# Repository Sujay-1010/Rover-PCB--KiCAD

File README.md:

# Rover-PCB--KiCAD
Following pcb contains a rover pcb design, its schematics, its bom(bill of materials), and the working paramters of all the components used.

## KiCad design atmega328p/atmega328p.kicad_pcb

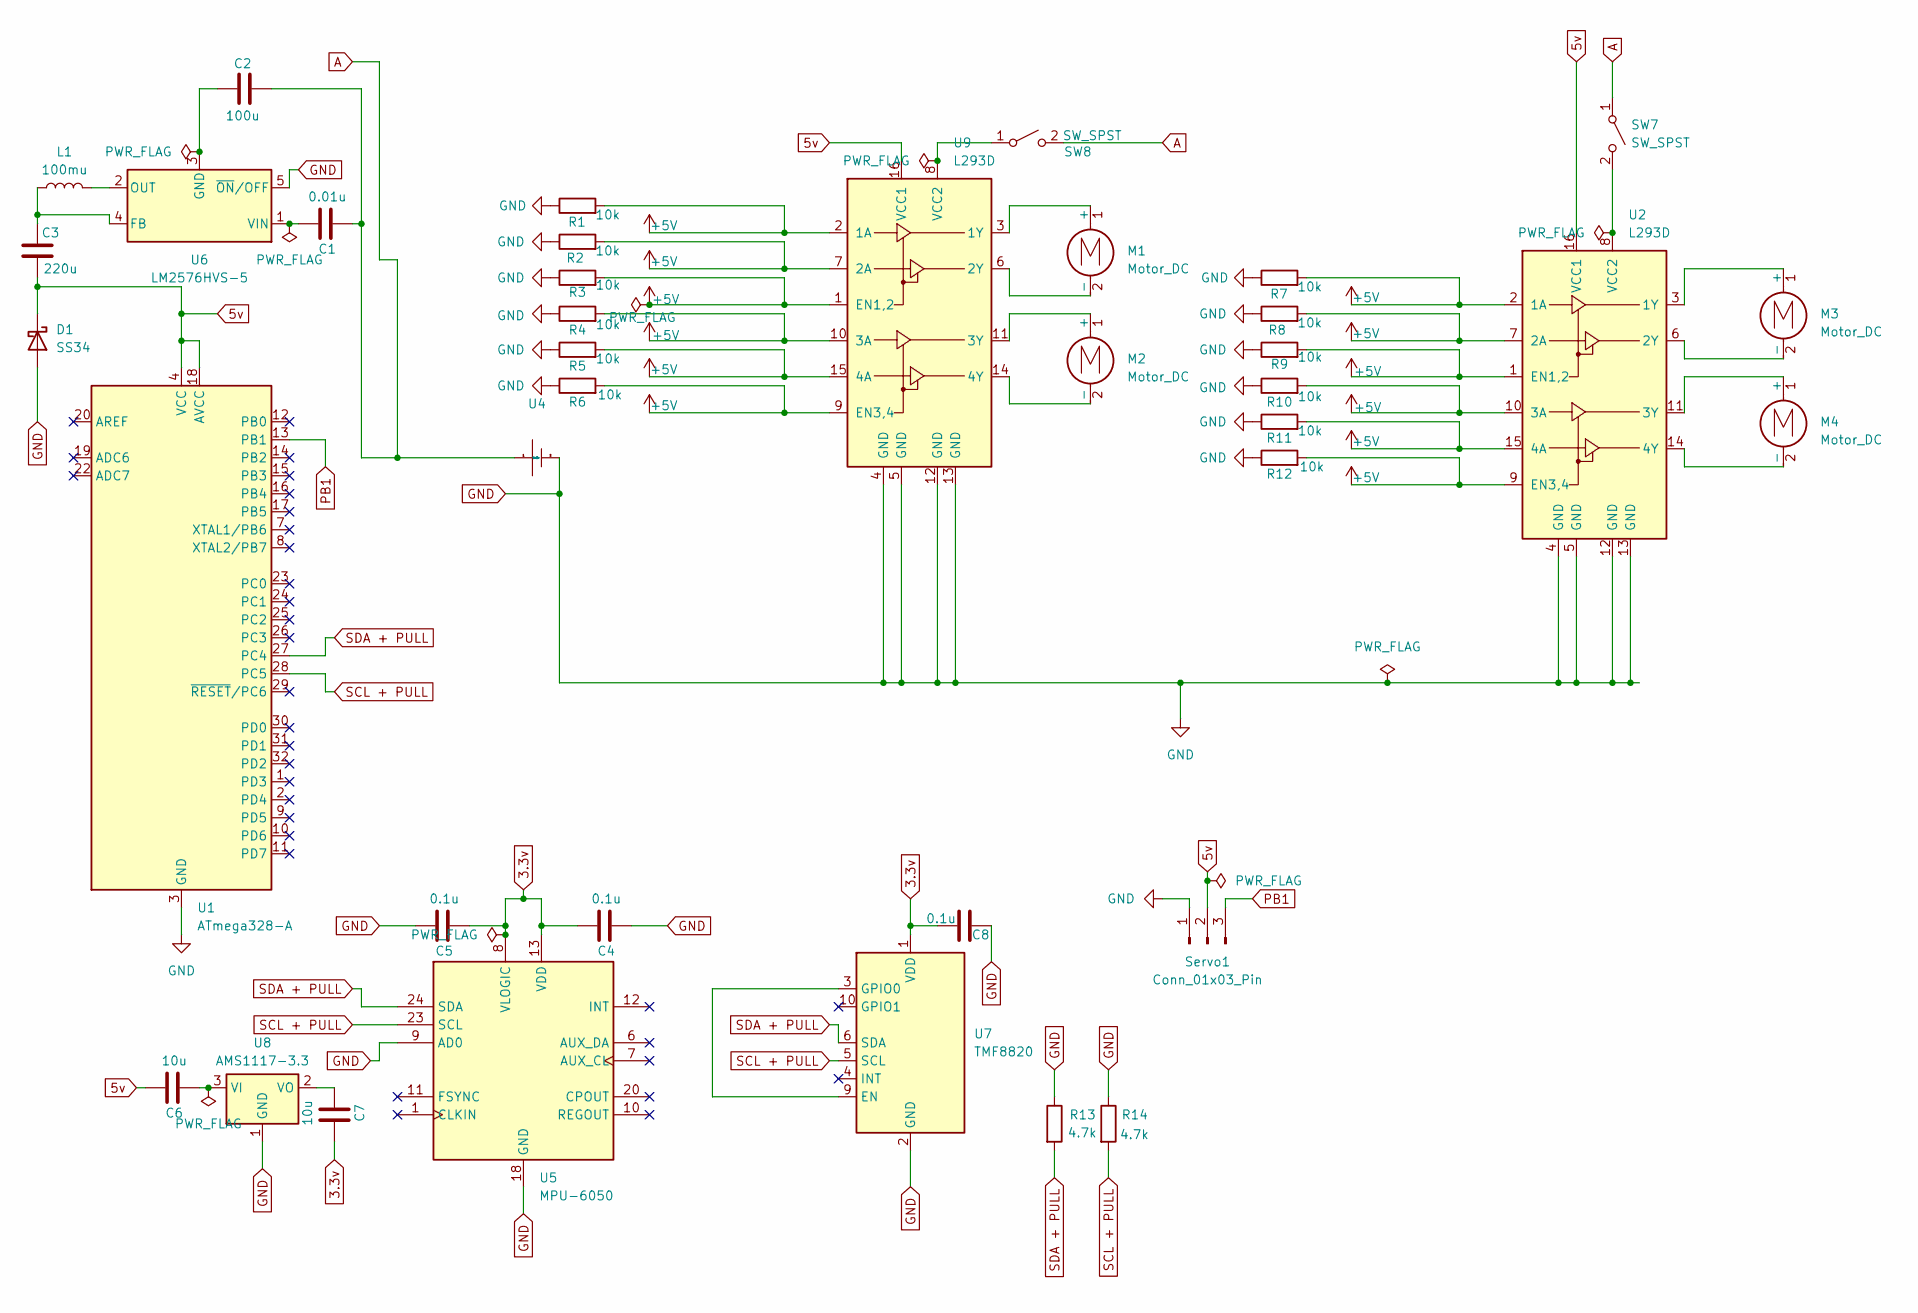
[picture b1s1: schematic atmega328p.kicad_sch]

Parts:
C1: 0.01u; C_0603_1608Metric
C2: 100u; C_0603_1608Metric
C3: 220u; C_0603_1608Metric
C4, C5, C8: 0.1u; C_0603_1608Metric
C6, C7: 10u; C_0805_2012Metric
D1: SS34; D_SMA
L1: 100mu; L_10.4x10.4_H4.8
M1, M2, M3, M4: Motor_DC; TerminalBlock_Phoenix_MKDS-1,5-2-5.08_1x02_P5.08mm_Horizont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
R1, R2, R3, R4, R5, R6, R7, R8, R9, R10, R11, R12: 10k; R_0603_1608Metric
R13, R14: 4.7k; R_0603_1608Metric
SW7, SW8: SW_SPST; SW_Push_1P1T_NO_CK_KMR2
Servo1: Conn_01x03_Pin; PinHeader_1x03_P2.54mm_Vertical_SMD_Pin1Left
U1: ATmega328-A; TQFP-32_7x7mm_P0.8mm
U2, U9: L293D; SOIC-16_3.9x9.9mm_P1.27mm
U4: AMASS_XT30PW-F_1x02_P2.50mm_Horizontal
U5: MPU-6050; InvenSense_QFN-24_4x4mm_P0.5mm
U6: LM2576HVS-5; TO-263-5_TabPin3
U7: TMF8820; AMS_OLGA12
U8: AMS1117-3.3; SOT-223-3_TabPin2

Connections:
3.3v: C4.1, C5.2, C7.1, C8.1, U5.8 (VLOGIC), U5.13 (VDD), U7.1 (VDD), U7.7 (VDD), U7.12 (VDD)
5v: C3.1, C6.1, D1.1 (K), Servo1.2, U1.4 (VCC), U1.6 (VCC), U1.18 (AVCC), U2.16 (VCC1), U9.16 (VCC1)
+5V: R1.2, R2.2, R3.2, R4.2, R5.2, R6.2, R7.2, R8.2, R9.2, R10.2, R11.2, R12.2, U2.1 (EN1,2), U2.2 (1A), U2.7 (2A), U2.9 (EN3,4), U2.10 (3A), U2.15 (4A), U9.1 (EN1,2), U9.2 (1A), U9.7 (2A), U9.9 (EN3,4), U9.10 (3A), U9.15 (4A)
A: C1.2, C2.1, SW7.1 (A), SW8.2 (B), U4.1 (5v)
GND: C4.2, C5.1, C8.2, D1.2 (A), R1.1, R2.1, R3.1, R4.1, R5.1, R6.1, R7.1, R8.1, R9.1, R10.1, R11.1, R12.1, R13.1, R14.1, Servo1.1, U1.3 (GND), U1.5 (GND), U1.21 (GND), U2.4 (GND), U2.5 (GND), U2.12 (GND), U2.13 (GND), U4.2 (Gnd), U5.9 (AD0), U5.18 (GND), U6.5 (~ON/OFF), U7.2 (GND), U7.8 (GND), U7.11 (GND), U8.1 (GND), U9.4 (GND), U9.5 (GND), U9.12 (GND), U9.13 (GND)
unnamed: M1.1 (+), U9.3 (1Y)
unnamed: M1.2 (-), U9.6 (2Y)
unnamed: M2.1 (+), U9.11 (3Y)
unnamed: M2.2 (-), U9.14 (4Y)
unnamed: M3.1 (+), U2.3 (1Y)
unnamed: M3.2 (-), U2.6 (2Y)
unnamed: M4.1 (+), U2.11 (3Y)
unnamed: M4.2 (-), U2.14 (4Y)
unnamed: SW7.2 (B), U2.8 (VCC2)
unnamed: SW8.1 (A), U9.8 (VCC2)
unnamed: C3.2, L1.1, U6.4 (FB)
unnamed: C2.2, U6.3 (GND)
unnamed: L1.2, U6.2 (OUT)
unnamed: C1.1, U6.1 (VIN)
unnamed: U7.3 (GPIO0), U7.9 (EN)
unnamed: C6.2, U8.3 (VI)
unnamed: C7.2, U8.2 (VO)
PB1: Servo1.3, U1.13 (PB1)
SCL + PULL: R14.2, U1.28 (PC5), U5.23 (SCL), U7.5 (SCL)
SDA + PULL: R13.2, U1.27 (PC4), U5.24 (SDA), U7.6 (SDA)

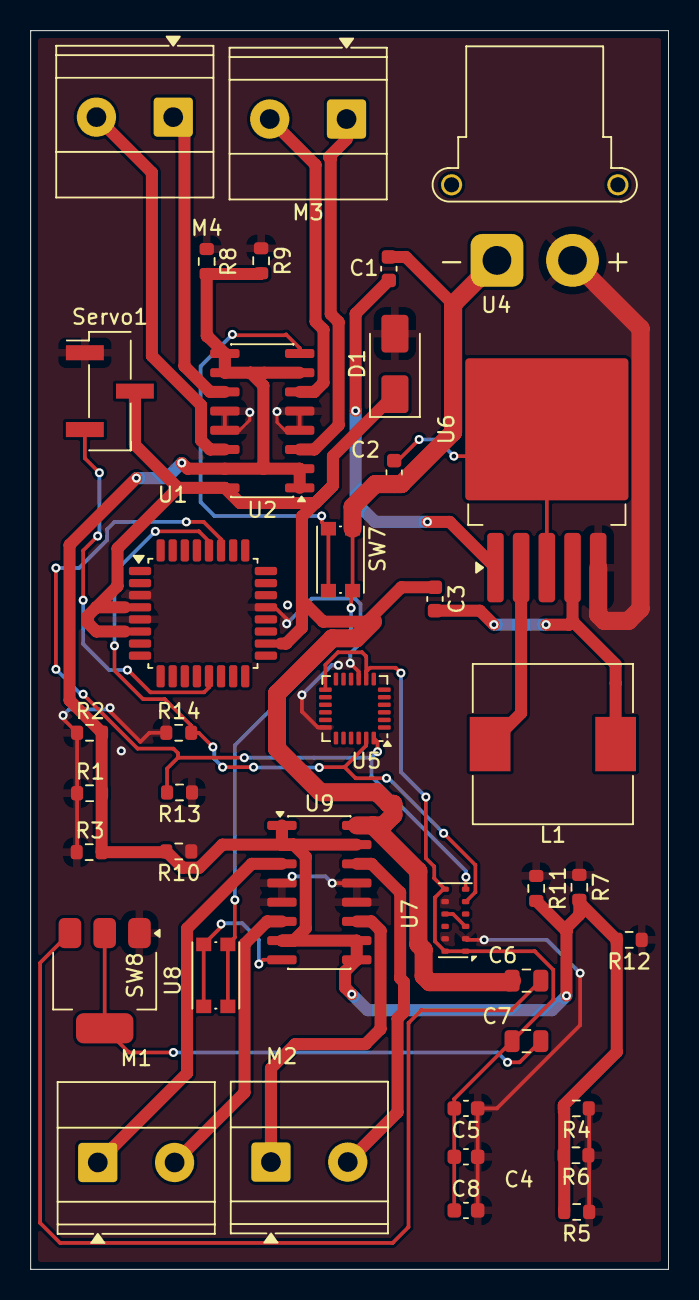
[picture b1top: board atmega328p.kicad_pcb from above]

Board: 2 copper layers, 42.2 x 81.9 mm, 39 parts (0 on the bottom side), 25 nets.

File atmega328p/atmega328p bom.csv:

"Reference","Qty","Value","DNP","Exclude from BOM","Exclude from Board","Footprint","Datasheet"
"C1","1","0.01u","","","","Capacitor_SMD:C_0603_1608Metric","~"
"C2","1","100u","","","","Capacitor_SMD:C_0603_1608Metric","~"
"C3","1","220u","","","","Capacitor_SMD:C_0603_1608Metric","~"
"C4,C5,C8","3","0.1u","","","","Capacitor_SMD:C_0603_1608Metric","~"
"C6,C7","2","10u","","","","Capacitor_SMD:C_0805_2012Metric","~"
"D1","1","SS34","","","","Diode_SMD:D_SMA","https://www.vishay.com/docs/88751/ss32.pdf"
"L1","1","100mu","","","","Inductor_SMD:L_10.4x10.4_H4.8","~"
"M1,M2,M3,M4","4","Motor_DC","","","","TerminalBlock_Phoenix:TerminalBlock_Phoenix_MKDS-1,5-2-5.08_1x02_P5.08mm_Horizontal","~"
"R1,R2,R3,R4,R5,R6,R7,R8,R9,R10,R11,R12","12","10k","","","","Resistor_SMD:R_0603_1608Metric","~"
"R13,R14","2","4.7k","","","","Resistor_SMD:R_0603_1608Metric","~"
"Servo1","1","Conn_01x03_Pin","","","","Connector_PinHeader_2.54mm:PinHeader_1x03_P2.54mm_Vertical_SMD_Pin1Left","~"
"SW7,SW8","2","SW_SPST","","","","Button_Switch_SMD:SW_Push_1P1T_NO_CK_KMR2","~"
"U1","1","ATmega328-A","","","","Package_QFP:TQFP-32_7x7mm_P0.8mm","http://ww1.microchip.com/downloads/en/DeviceDoc/ATmega328_P%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"
"U2,U9","2","L293D","","","","Package_SO:SOIC-16_3.9x9.9mm_P1.27mm","http://www.ti.com/lit/ds/symlink/l293.pdf"
"U4","1","~","","","","Connector_JST:JST_PH_B2B-PH-K_1x02_P2.00mm_Vertical",""
"U5","1","MPU-6050","","","","Sensor_Motion:InvenSense_QFN-24_4x4mm_P0.5mm","https://invensense.tdk.com/wp-content/uploads/2015/02/MPU-60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"
"U6","1","LM2576HVS-5","","","","Package_TO_SOT_SMD:TO-263-5_TabPin3","http://www.ti.com/lit/ds/symlink/lm2576.pdf"
"U7","1","TMF8820","","","","Sensor_Distance:AMS_OLGA12","https://ams.com/documents/20143/6015057/TMF882X_DS000693_8-00.pdf"
"U8","1","AMS1117-3.3","","","","Package_TO_SOT_SMD:SOT-223-3_TabPin2","http://www.advanced-monolithic.com/pdf/ds1117.pdf"
